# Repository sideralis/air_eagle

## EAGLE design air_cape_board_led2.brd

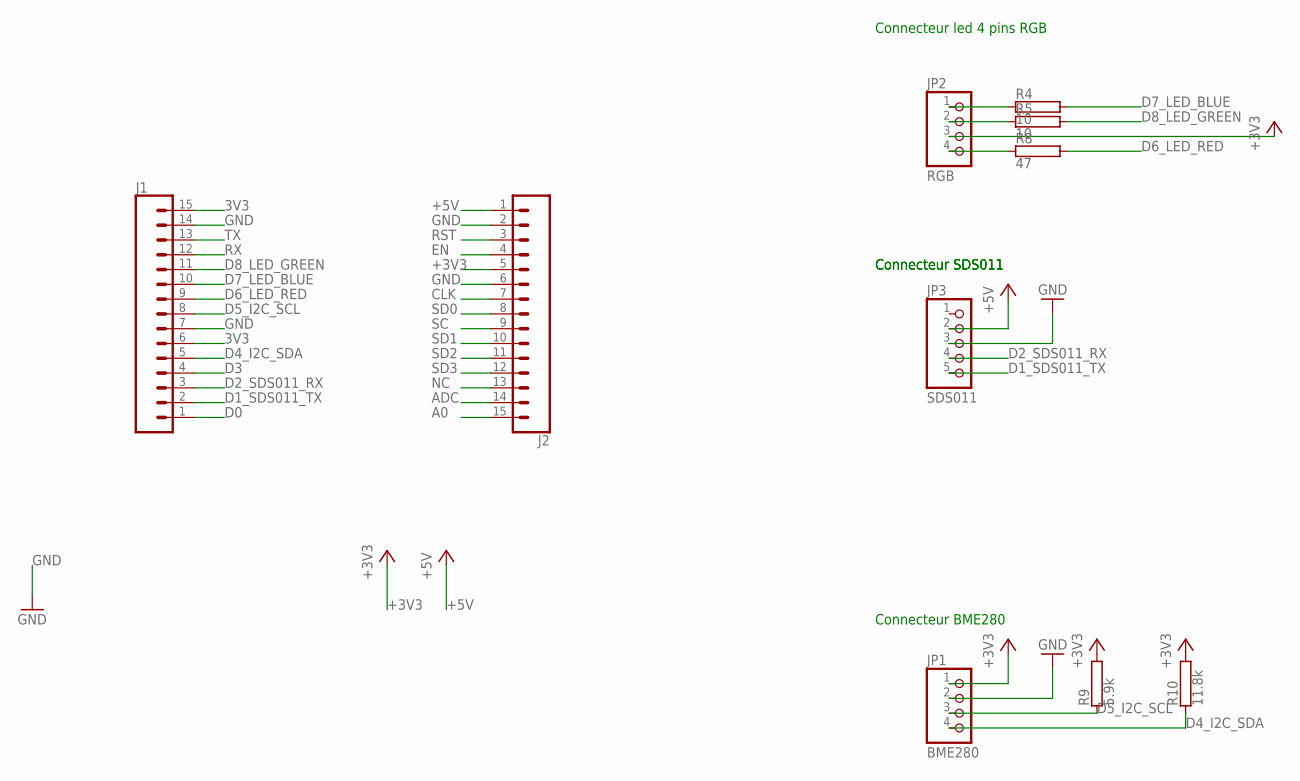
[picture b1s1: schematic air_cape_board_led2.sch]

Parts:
J1, J2: CONN_15; 1X15
JP1: BME280; 1X04
JP2: RGB; 1X04
JP3: SDS011; 1X05
R4, R5: 10; RS1/4
R8: 47; RS1/4
R9: 5.9k; RS1/4
R10: 11.8k; RS1/4

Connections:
3V3: J1.6, J1.15
+3V3: J2.5, JP1.1, JP2.3, R9.2, R10.2
+5V: J2.1, JP3.2
A0: J2.15
ADC: J2.14
CLK: J2.7
D0: J1.1
D1_SDS011_TX: J1.2, JP3.5
D2_SDS011_RX: J1.3, JP3.4
D3: J1.4
D4_I2C_SDA: J1.5, JP1.4, R10.1
D5_I2C_SCL: J1.8, JP1.3, R9.1
D6_LED_RED: J1.9, R8.2
D7_LED_BLUE: J1.10, R4.2
D8_LED_GREEN: J1.11, R5.2
EN: J2.4
GND: J1.7, J1.14, J2.2, J2.6, JP1.2, JP3.3
unnamed: JP2.4, R8.1
unnamed: JP2.2, R5.1
unnamed: JP2.1, R4.1
NC: J2.13
RST: J2.3
RX: J1.12
SC: J2.9
SD0: J2.8
SD1: J2.10
SD2: J2.11
SD3: J2.12
TX: J1.13

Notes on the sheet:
Connecteur SDS011
Connecteur BME280
Connecteur led 4 pins RGB

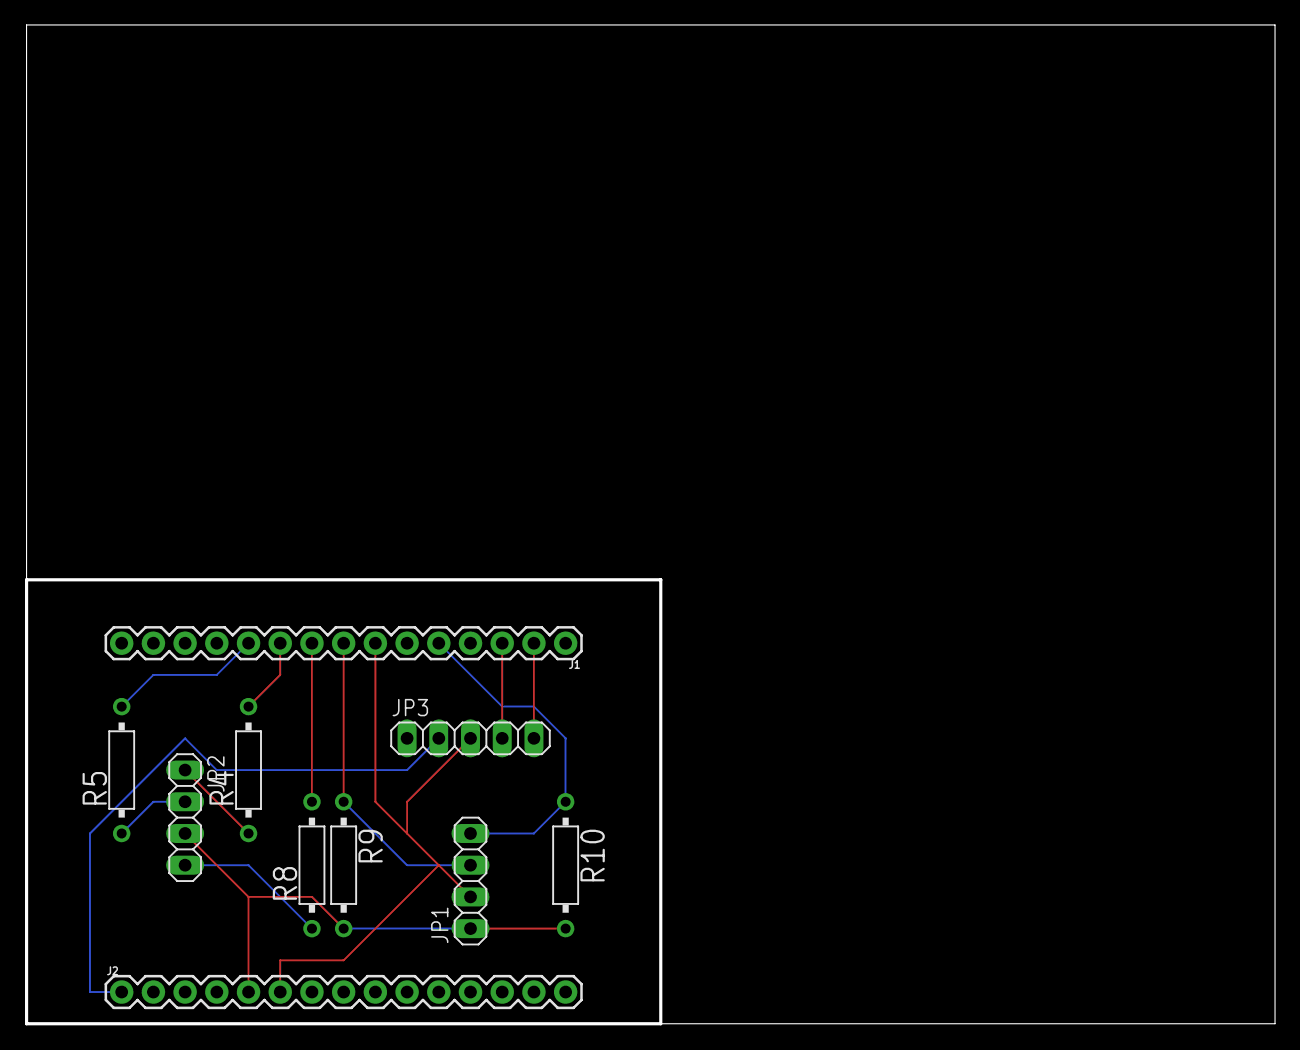
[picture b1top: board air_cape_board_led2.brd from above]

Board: 2 copper layers, 100.0 x 80.0 mm, 10 parts (0 on the bottom side), 14 nets.

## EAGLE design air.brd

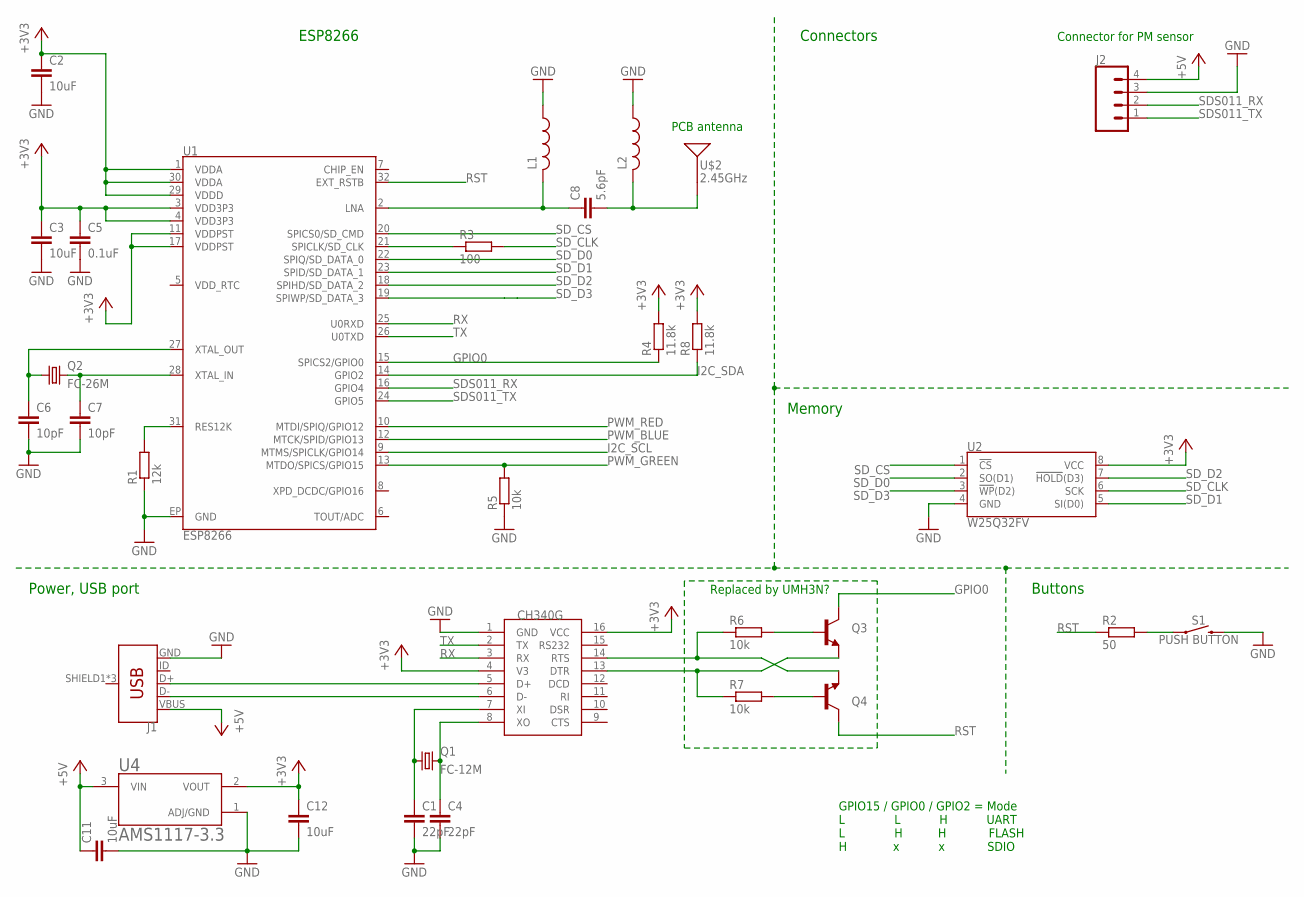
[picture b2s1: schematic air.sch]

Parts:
C1, C4: 22pF; C1206
C2, C3, C11, C12: 10uF; C1206
C5: 0.1uF; C1206
C6, C7: 10pF; C1206
C8: 5.6pF; C1206
J1: USB_MICRO-B_FEMALE-SMT; USB-B-MICRO-SMD
J2: CONN_04JST-PTH-VERT; JST-4-PTH-VERT
L1, L2: L-USL1812; L1812
Q1: FC-12M
Q2: FC-26M; FC-12M
Q3, Q4: BC849SMD; SOT23-BEC
R1: 12k; R0805
R2: 50; R0805
R3: 100; R0805
R4, R8: 11.8k; R0805
R5, R6, R7: 10k; R0805
S1: PUSH BUTTON; TACTILE_SWITCH_PTH_6.0MM
U1: ESP8266; QFN32-5X5MM
U2: W25Q32FV; SOIC-8
U3: CH340G; SOIC16
U4: AMS1117-3.3; SOT229P700X180-4N
U$2: 2.45GHz; ANT-2.4GHZ-6.5X2.2MM

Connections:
+3V3: C2.1, C3.1, C5.1, C12.1, R4.2, R8.2, U1.1 (VDDA), U1.3 (VDD3P3), U1.4 (VDD3P3), U1.11 (VDDPST), U1.17 (VDDPST), U1.29 (VDDD), U1.30 (VDDA), U2.8 (VCC), U3.4 (V3), U3.16 (VCC), U4.2 (VOUT)
+5V: C11.1, J1.VBUS, J2.4, U4.3 (VIN)
GND: C1.2, C2.2, C3.2, C4.2, C5.2, C6.2, C7.2, C11.2, C12.2, J1.GND, J2.3, L1.1, L2.1, R1.1, R5.1, S1.3 (2), U1.EP (GND), U2.4 (GND), U3.1 (GND), U4.1 (ADJ/GND)
GPIO0: Q3.C, R4.1, U1.15 (SPICS2/GPIO0)
unnamed: R3.1, U1.21 (SPICLK/SD_CLK)
unnamed: C6.1, Q2.1, U1.27 (XTAL_OUT)
unnamed: J1.D+, U3.5 (D+)
unnamed: C7.1, Q2.2, U1.28 (XTAL_IN)
unnamed: R1.2, U1.31 (RES12K)
unnamed: J1.D-, U3.6 (D-)
unnamed: C1.1, Q1.1, U3.7 (XI)
unnamed: C4.1, Q1.2, U3.8 (XO)
unnamed: R2.2, S1.1
unnamed: C8.1, L1.2, U1.2 (LNA)
unnamed: C8.2, L2.2, U$2.FEED
unnamed: R8.1, U1.14 (GPIO2)
unnamed: Q4.E, R6.1, U3.14 (RTS)
unnamed: Q3.E, R7.1, U3.13 (DTR)
unnamed: Q3.B, R6.2
unnamed: Q4.B, R7.2
PWM_BLUE: U1.9 (MTMS/SPICLK/GPIO14)
PWM_GREEN: R5.2, U1.13 (MTDO/SPICS/GPIO15)
PWM_RED: U1.10 (MTDI/SPIQ/GPIO12)
RST: Q4.C, R2.1, U1.32 (EXT_RSTB)
RX: U1.25 (U0RXD), U3.3 (RX)
SDS011_RX: J2.2, U1.16 (GPIO4)
SDS011_TX: J2.1, U1.24 (GPIO5)
SD_CLK: R3.2, U2.6 (SCK)
SD_CS: U1.20 (SPICS0/SD_CMD), U2.1 (!CS!)
SD_D0: U1.22 (SPIQ/SD_DATA_0), U2.2 (SO(D1))
SD_D1: U1.23 (SPID/SD_DATA_1), U2.5 (SI(D0))
SD_D2: U1.18 (SPIHD/SD_DATA_2), U2.7 (!HOLD!(D3))
SD_D3: U1.19 (SPIWP/SD_DATA_3), U2.3 (!WP!(D2))
TX: U1.26 (U0TXD), U3.2 (TX)

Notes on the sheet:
Replaced by UMH3N?
PCB antenna
Connector for PM sensor
Memory
Power, USB port
ESP8266
Connectors
Buttons
GPIO15 / GPIO0 / GPIO2 = Mode L L H UART L H H FLASH H x x SDIO

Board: 2 copper layers, 32 parts (0 on the bottom side), 32 nets, no tracks yet.

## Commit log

2018-05-24 adding gitignore to ignore eagle backup files
2018-05-25 Switch to SMD, change voltage regulator, fix errors
2018-06-27 Add capeboard schematic and led on main schematic
2018-07-24 Cape board completed
    - Replace 3 Clor LED by simple RGB LED
    - Placement and routing done
2018-07-25 Fix issue with led power supply
    - Should be VDD instead of GND
2018-08-05 Schematic and layout for led with common set to VDD

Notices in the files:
parts and their libraries:
SparkFun-Connectors: Licensing: Creative Commons ShareAlike 4.0 International - https://creativecommons.org/licenses/by-sa/4.0
